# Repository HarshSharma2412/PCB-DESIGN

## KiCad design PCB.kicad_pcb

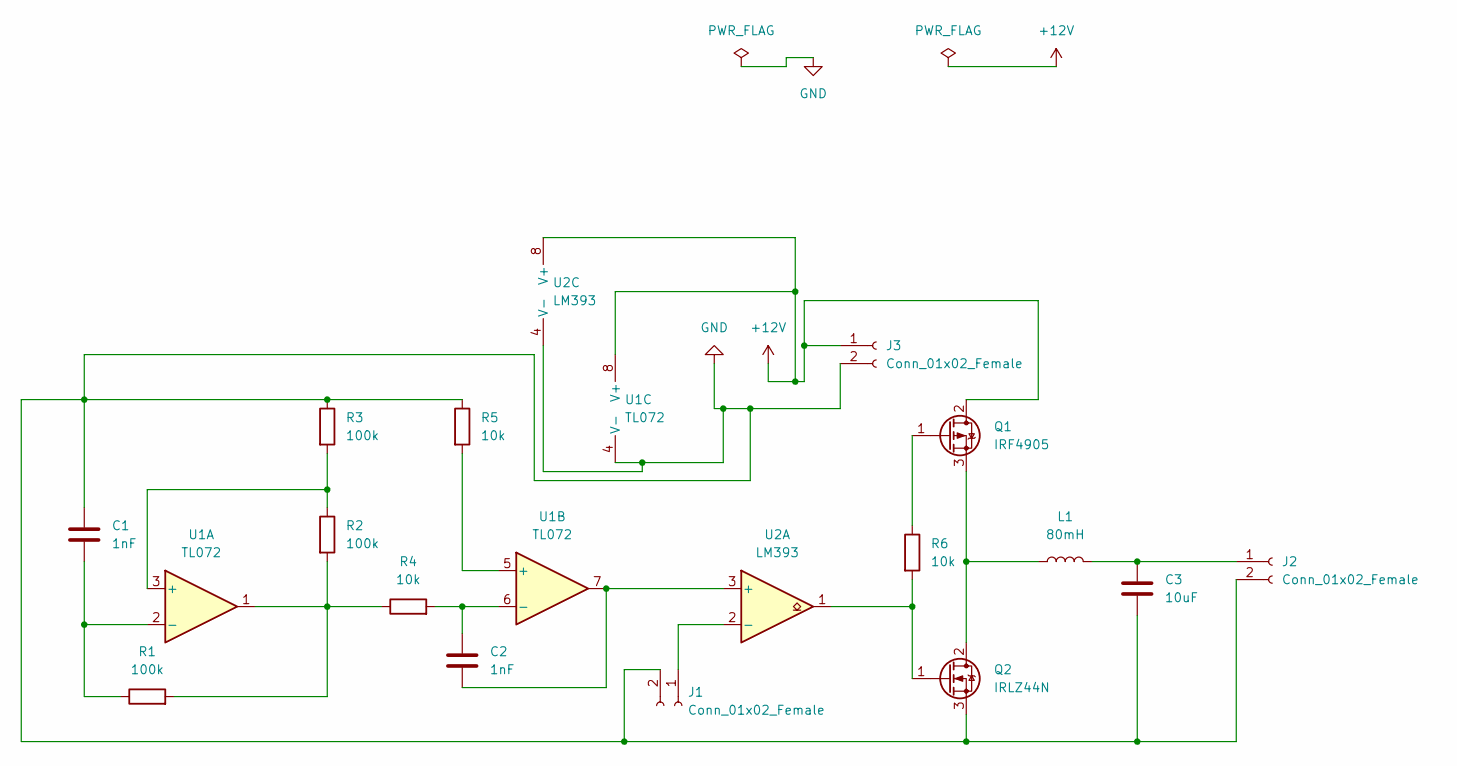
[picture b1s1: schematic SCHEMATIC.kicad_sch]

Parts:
C1, C2: 1nF; C_0603_1608Metric
C3: 10uF; C_0603_1608Metric
J1, J2, J3: Conn_01x02_Female; PinHeader_1x02_P2.54mm_Vertical
L1: 80mH; L_1206_3216Metric
Q1: IRF4905; TO-220-3_Vertical
Q2: IRLZ44N; TO-220-3_Vertical
R1, R2, R3: 100k; R_0603_1608Metric
R4, R5, R6: 10k; R_0603_1608Metric
U1: TL072; DIP-8_W7.62mm
U2: LM393; DIP-8_W7.62mm

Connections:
+12V: J3.1, Q1.2 (D), U1.8 (V+), U2.8 (V+)
GND: C1.1, C3.2, J1.2, J2.2, J3.2, Q2.3 (S), R3.1, R5.1, U1.4 (V-), U2.4 (V-)
unnamed: C2.2, U1.7, U2.3 (+)
unnamed: L1.1, Q1.3 (S), Q2.2 (D)
unnamed: C3.1, J2.1, L1.2
unnamed: C1.2, R1.1, U1.2 (-)
unnamed: R1.2, R2.2, R4.1, U1.1
unnamed: R2.1, R3.2, U1.3 (+)
unnamed: C2.1, R4.2, U1.6 (-)
unnamed: R5.2, U1.5 (+)
unnamed: Q1.1 (G), R6.1
unnamed: Q2.1 (G), R6.2, U2.1
unnamed: J1.1, U2.2 (-)

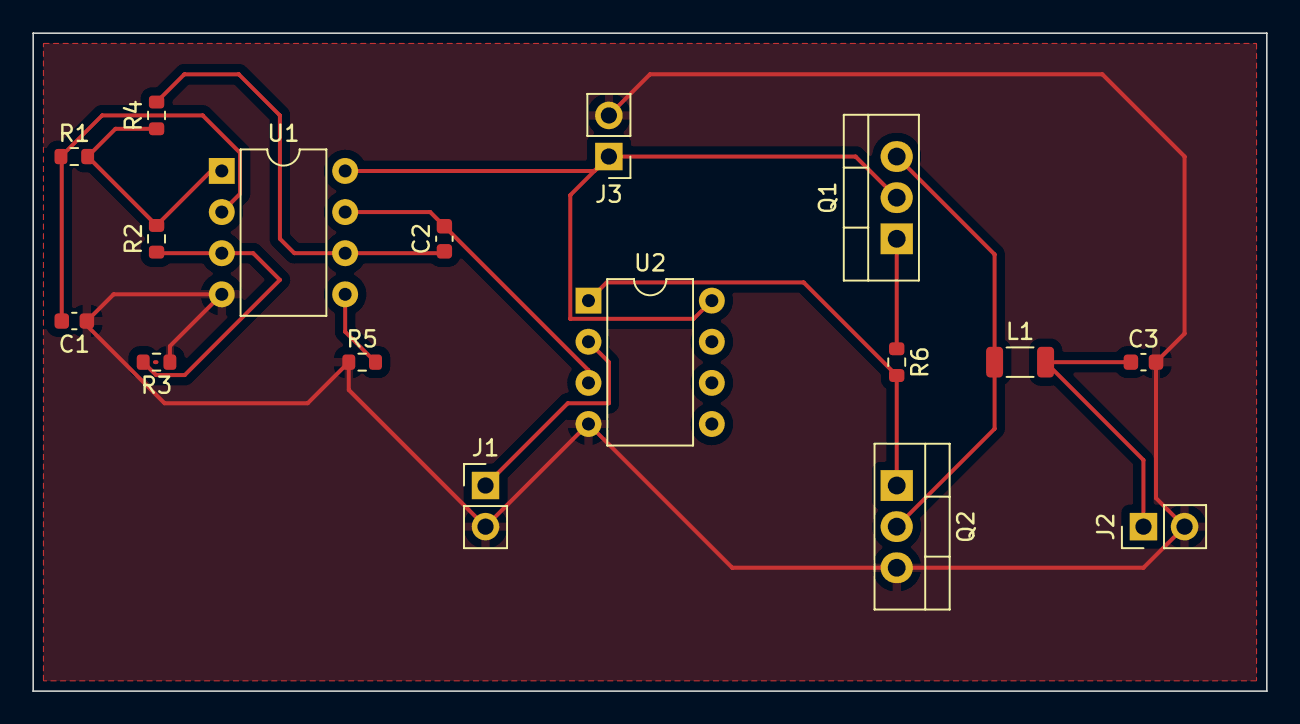
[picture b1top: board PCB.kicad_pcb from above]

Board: 2 copper layers, 76.2 x 40.6 mm, 17 parts (0 on the bottom side), 13 nets.
